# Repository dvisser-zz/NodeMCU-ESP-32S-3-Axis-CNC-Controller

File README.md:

# NodeMCU-ESP-32S-3-Axis-CNC-Controller

## 3-Axis CNC Controller using Trinamic TMC5160 drivers.

### Runs the GRBL-ESP32 firmware by bdring found here https://github.com/bdring/Grbl_Esp32/tree/TMCStepper

###### Board Specifications:

- 24V DC nominal motor/board supply voltage 
  - Working Range
    - 18V DC (min)
    - 36V DC (max)
- Based on ESP32 MCU
- 3 x stepper drivers (TMC5160) to suit 3-axis machines
- Multiple spindle control options 
  - 3.3V PWM output
  - 0-5V analog DC output
  - 0-10V analog DC output (op-amp buffered)
  - 3.3V spindle enable binary output (works with 5v logic VFD binary inputs as well)
- Z Probe input (3.3V logic level)
- All screw terminals are 5.08mm pitch for reliability and durability
- On-board micro SD card support
- Spindle Coolant Relay (active when spindle is enabled) with LED indicator
- Tool/Cutting Coolant Relay (active with grbl mist output is enabled) with LED indicator
- 3 x power LED's (3.3V, 5V and 24V)

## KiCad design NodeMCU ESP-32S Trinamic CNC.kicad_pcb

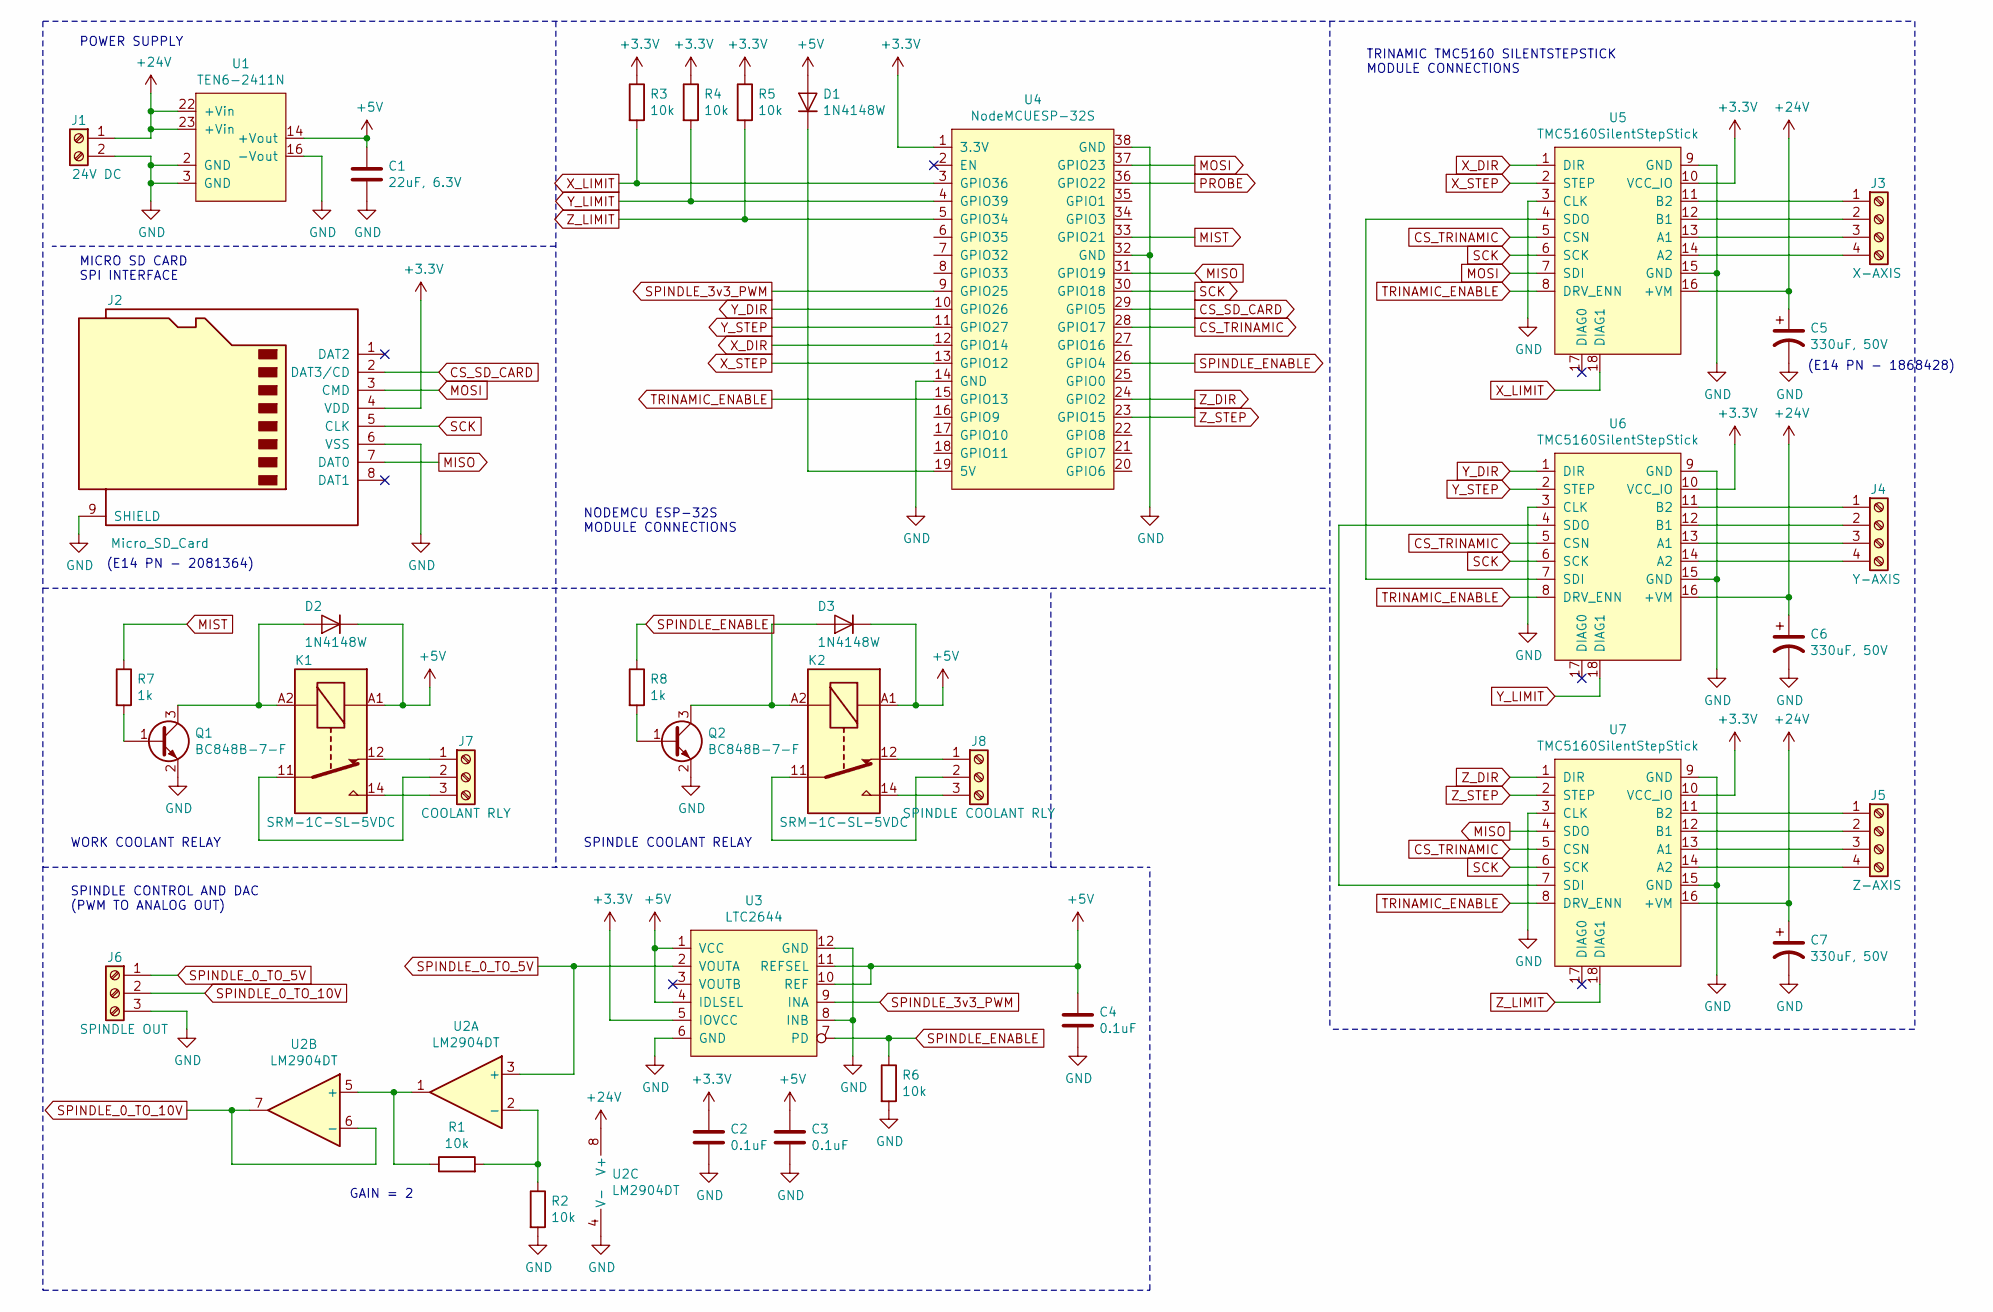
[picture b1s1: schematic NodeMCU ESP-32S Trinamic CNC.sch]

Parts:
C1: 22uF, 6.3V; C_0603_1608Metric
C2, C3, C4: 0.1uF; C_0603_1608Metric
C5, C6, C7: 330uF, 50V; CP_Elec_10x10.5
D1, D2, D3: 1N4148W; D_SOD-123
J1: 24V DC; TerminalBlock_bornier-2_P5.08mm
J2: Micro_SD_Card; microSD_HC_Wuerth_693072010801
J3: X-AXIS; TerminalBlock_bornier-4_P5.08mm
J4: Y-AXIS; TerminalBlock_bornier-4_P5.08mm
J5: Z-AXIS; TerminalBlock_bornier-4_P5.08mm
J6: SPINDLE OUT; TerminalBlock_bornier-3_P5.08mm
J7: COOLANT RLY; TerminalBlock_bornier-3_P5.08mm
J8: SPINDLE COOLANT RLY; TerminalBlock_bornier-3_P5.08mm
K1, K2: SRM-1C-SL-5VDC
Q1, Q2: BC848B-7-F; SOT-23
R1, R2, R3, R4, R5, R6: 10k; R_0603_1608Metric
R7, R8: 1k; R_0603_1608Metric
U1: TEN6-2411N
U2: LM2904DT; SO-8_3.9x4.9mm_P1.27mm
U3: LTC2644; MSOP-12_3x4mm_P0.65mm
U4: NodeMCUESP-32S
U5, U6, U7: TMC5160SilentStepStick

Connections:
+3V3: C2.1, J2.4 (VDD), R3.1, R4.1, R5.1, U3.5 (IOVCC), U4.1 (3.3V), U5.10 (VCC_IO), U6.10 (VCC_IO), U7.10 (VCC_IO)
+5V: C1.1, C3.1, C4.1, D1.2 (A), D2.1 (K), D3.1 (K), K1.A1, K2.A1, U1.14 (+Vout), U3.1 (VCC), U3.4 (IDLSEL), U3.10 (REF), U3.11 (REFSEL)
+24V: C5.1, C6.1, C7.1, J1.1, U1.22 (+Vin), U1.23 (+Vin), U2.8 (V+), U5.16 (+VM), U6.16 (+VM), U7.16 (+VM)
CS_SD_CARD: J2.2 (DAT3/CD), U4.29 (GPIO5)
CS_TRINAMIC: U4.28 (GPIO17), U5.5 (CSN), U6.5 (CSN), U7.5 (CSN)
GND: C1.2, C2.2, C3.2, C4.2, C5.2, C6.2, C7.2, J1.2, J2.6 (VSS), J2.9 (SHIELD), J6.3, Q1.2 (E), Q2.2 (E), R2.2, R6.2, U1.2 (GND), U1.3 (GND), U1.16 (-Vout), U2.4 (V-), U3.6 (GND), U3.8 (INB), U3.12 (GND), U4.14 (GND), U4.32 (GND), U4.38 (GND), U5.3 (CLK), U5.9 (GND), U5.15 (GND), U6.3 (CLK), U6.9 (GND), U6.15 (GND), U7.3 (CLK), U7.9 (GND), U7.15 (GND)
MISO: J2.7 (DAT0), U4.31 (GPIO19), U7.4 (SDO)
MIST: R7.1, U4.33 (GPIO21)
MOSI: J2.3 (CMD), U4.37 (GPIO23), U5.7 (SDI)
unnamed: D1.1 (K), U4.19 (5V)
unnamed: D2.2 (A), K1.A2, Q1.3 (C)
unnamed: D3.2 (A), K2.A2, Q2.3 (C)
unnamed: J3.1, U5.11 (B2)
unnamed: J3.2, U5.12 (B1)
unnamed: J3.3, U5.13 (A1)
unnamed: J3.4, U5.14 (A2)
unnamed: J4.1, U6.11 (B2)
unnamed: J4.2, U6.12 (B1)
unnamed: J4.3, U6.13 (A1)
unnamed: J4.4, U6.14 (A2)
unnamed: J5.1, U7.11 (B2)
unnamed: J5.2, U7.12 (B1)
unnamed: J5.3, U7.13 (A1)
unnamed: J5.4, U7.14 (A2)
unnamed: J7.1, K1.12
unnamed: J7.2, K1.11
unnamed: J7.3, K1.14
unnamed: J8.1, K2.12
unnamed: J8.2, K2.11
unnamed: J8.3, K2.14
unnamed: Q1.1 (B), R7.2
unnamed: Q2.1 (B), R8.2
unnamed: R1.1, U2.1, U2.5 (+)
unnamed: R1.2, R2.1, U2.2 (-)
unnamed: U5.4 (SDO), U6.7 (SDI)
unnamed: U6.4 (SDO), U7.7 (SDI)
PROBE: U4.36 (GPIO22)
SCK: J2.5 (CLK), U4.30 (GPIO18), U5.6 (SCK), U6.6 (SCK), U7.6 (SCK)
SPINDLE_0_TO_5V: J6.1, U2.3 (+), U3.2 (VOUTA)
SPINDLE_0_TO_10V: J6.2, U2.6 (-), U2.7
SPINDLE_3v3_PWM: U3.9 (INA), U4.9 (GPIO25)
SPINDLE_ENABLE: R6.1, R8.1, U3.7 (PD), U4.26 (GPIO4)
TRINAMIC_ENABLE: U4.15 (GPIO13), U5.8 (DRV_ENN), U6.8 (DRV_ENN), U7.8 (DRV_ENN)
X_DIR: U4.12 (GPIO14), U5.1 (DIR)
X_LIMIT: R3.2, U4.3 (GPIO36), U5.18 (DIAG1)
X_STEP: U4.13 (GPIO12), U5.2 (STEP)
Y_DIR: U4.10 (GPIO26), U6.1 (DIR)
Y_LIMIT: R4.2, U4.4 (GPIO39), U6.18 (DIAG1)
Y_STEP: U4.11 (GPIO27), U6.2 (STEP)
Z_DIR: U4.24 (GPIO2), U7.1 (DIR)
Z_LIMIT: R5.2, U4.5 (GPIO34), U7.18 (DIAG1)
Z_STEP: U4.23 (GPIO15), U7.2 (STEP)

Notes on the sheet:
GAIN = 2
SPINDLE CONTROL AND DAC (PWM TO ANALOG OUT)
(E14 PN - 2081364)
MICRO SD CARD SPI INTERFACE
NODEMCU ESP-32S MODULE CONNECTIONS
POWER SUPPLY
TRINAMIC TMC5160 SILENTSTEPSTICK MODULE CONNECTIONS
(E14 PN - 1868428)
WORK COOLANT RELAY
SPINDLE COOLANT RELAY

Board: 2 copper layers, 37 parts (0 on the bottom side), 51 nets, no tracks yet.

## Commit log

2019-08-22 First release with gerber files included.
2019-08-22 Updated PDF schematic.
